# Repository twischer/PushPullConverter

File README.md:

PushPullConverter
=================

Half-bridge push-pull converter to convert 12 volt to higher voltage

There are assembled circuits available which reduces the complexity of this circuit and
might improve the efficiency.
Search for "EG7500 Inverter switching power driver board compatible KA7500 TL494" to find them.

Status
------
I am able to light up a 60W light bulb without rectifier secondary site in use.
But when using the rectifier the efficiency drops to ~50%.

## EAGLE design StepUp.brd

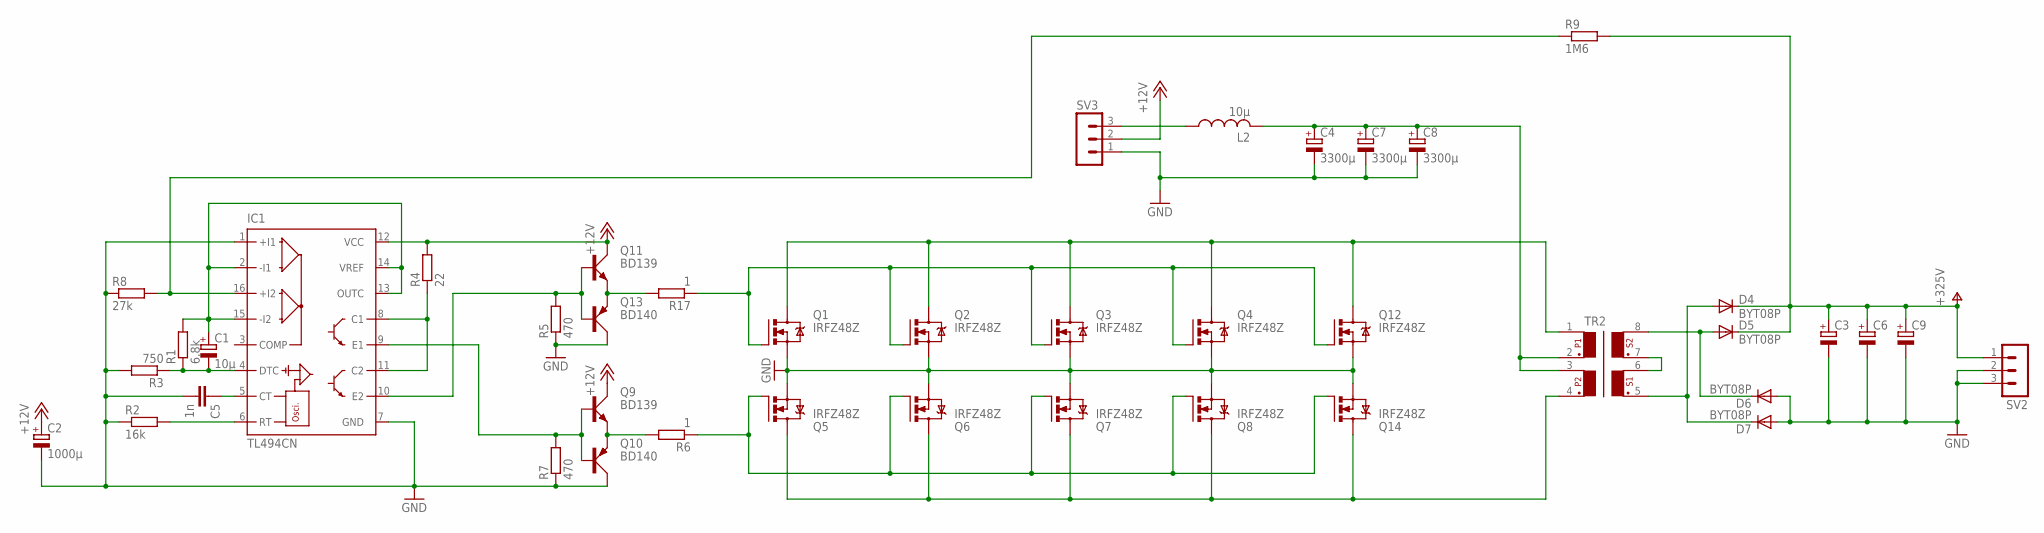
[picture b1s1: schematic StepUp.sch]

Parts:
C1: 10µ; E2,5-5
C2: 1000µ; E5-8,5
C3, C6, C9: CPOL-EUE3.5-8; E3,5-8
C4, C7, C8: 3300µ; E5-8,5
C5: 1n; C025-024X044
D4, D5, D6, D7: BYT08P; TO220ACS
IC1: TL494CN; DIL16
L2: 10µ; 6000-XXXX-RC
Q1, Q2, Q3, Q4, Q5, Q6, Q7, Q8, Q12, Q14: IRFZ48Z; TO220BH
Q9, Q11: BD139; TO126AV
Q10, Q13: BD140; TO126AV
R1: 6,8k; 0204V
R2: 16k; 0204V
R3: 750; 0204V
R4: 22; 0204V
R5, R7: 470; 0204V
R6, R17: 1; 0204V
R8: 27k; 0204/7
R9: 1M6; 0207/15
SV2, SV3: MA03-1
TR2: FL02; FL02-08

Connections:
+12V: C2.+, IC1.12 (VCC), Q9.C, Q11.C, R4.2, SV3.2
GND: C2.-, C3.-, C4.-, C5.2, C6.-, C7.-, C8.-, C9.-, D6.A, D7.A, IC1.1 (+I1), IC1.7 (GND), Q1.S, Q2.S, Q3.S, Q4.S, Q5.S, Q6.S, Q7.S, Q8.S, Q10.C, Q12.S, Q13.C, Q14.S, R2.1, R3.2, R5.1, R7.1, R8.1, SV2.2, SV2.3, SV3.1
unnamed: L2.1, SV3.3
unnamed: C5.1, IC1.5 (CT)
unnamed: C1.+, IC1.2 (-I1), IC1.13 (OUTC), IC1.14 (VREF), IC1.15 (-I2), R1.2
unnamed: IC1.16 (+I2), R8.2, R9.1
unnamed: C1.-, IC1.4 (DTC), R1.1, R3.1
unnamed: IC1.6 (RT), R2.2
unnamed: TR2.6, TR2.7
unnamed: Q11.E, Q13.E, R17.2
unnamed: Q1.G, Q2.G, Q3.G, Q4.G, Q12.G, R17.1
unnamed: IC1.8 (C1), IC1.11 (C2), R4.1
unnamed: IC1.10 (E2), Q11.B, Q13.B, R5.2
unnamed: Q5.G, Q6.G, Q7.G, Q8.G, Q14.G, R6.1
unnamed: Q9.E, Q10.E, R6.2
unnamed: IC1.9 (E1), Q9.B, Q10.B, R7.2
unnamed: D5.A, D6.C, TR2.8
unnamed: D4.A, D7.C, TR2.5
unnamed: Q5.D, Q6.D, Q7.D, Q8.D, Q14.D, TR2.4
unnamed: Q1.D, Q2.D, Q3.D, Q4.D, Q12.D, TR2.1
unnamed: C4.+, C7.+, C8.+, L2.2, TR2.2, TR2.3
V+: C3.+, C6.+, C9.+, D4.C, D5.C, R9.2, SV2.1

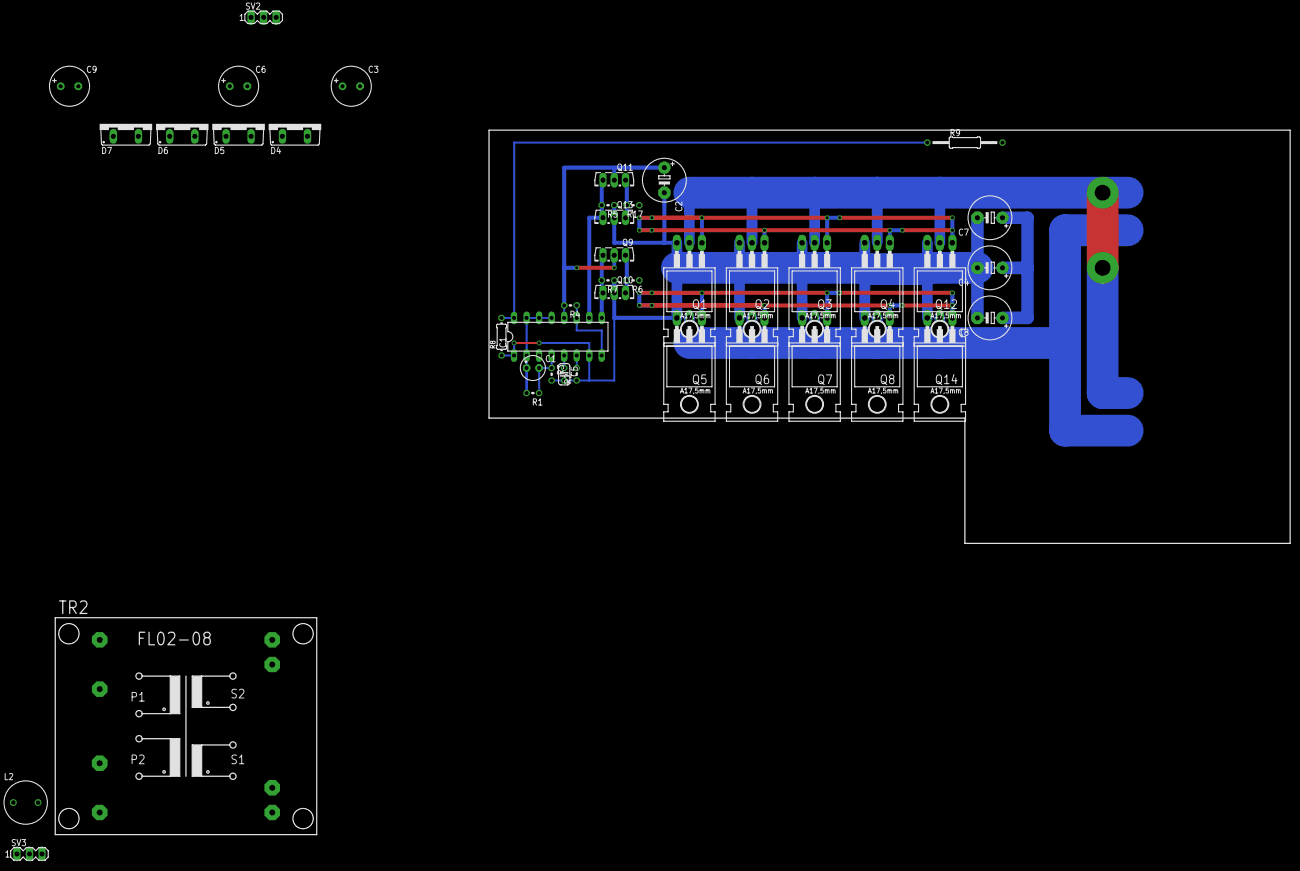
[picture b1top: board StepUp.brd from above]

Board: 2 copper layers, 162.5 x 83.8 mm, 42 parts (0 on the bottom side), 22 nets.

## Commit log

2014-10-07 Use simple MOSFET driver (only usefull for small MOSFETs
2014-10-07 Use class C bridge as MOSFET driver
2021-01-15 Add license
2021-01-15 Update current status
2021-01-15 Convert to kicad
